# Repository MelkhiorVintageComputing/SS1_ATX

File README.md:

An adapter to use an ATX power supply with a Sun SPARCstation 1, 1+, 2, or Sun 3/80. Use at your own risk.

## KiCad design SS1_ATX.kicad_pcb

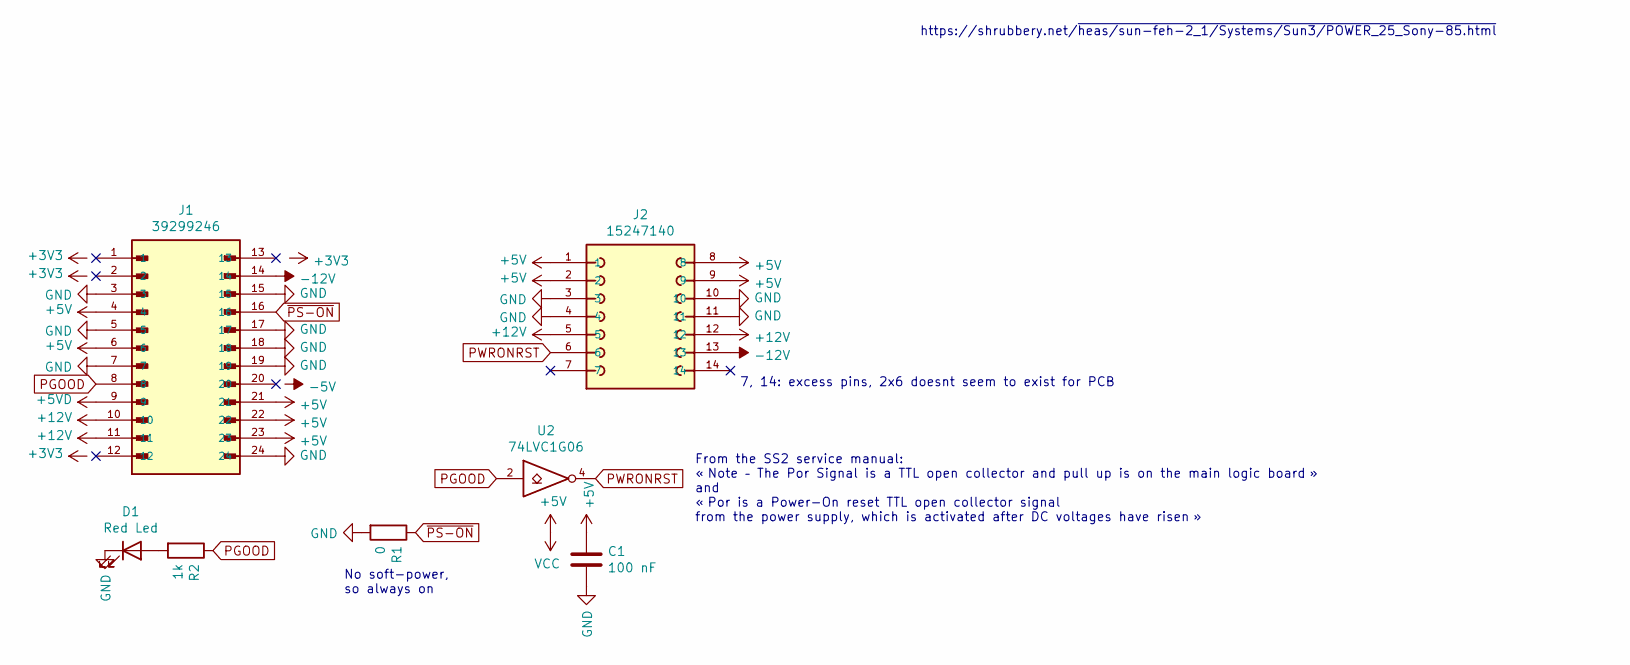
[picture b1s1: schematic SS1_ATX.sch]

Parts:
C1: 100 nF; C_0603_1608Metric; MPN CC0603KRX7R9BB104
D1: Red Led; LED_0805_2012Metric; MPN LTST-C170KRKT
J1: 39299246; MOLEX_39299246; PARTREV A1
J2: 15247140; MOLEX_15247140; PARTREV X5
R1: 0; R_0603_1608Metric; MPN 0603WAF0000T5E
R2: 1k; R_0603_1608Metric; MPN 0603WAF1001T5E
U2: 74LVC1G06; SOT-23-5; MPN SN74LVC1G06DBVR

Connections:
+5V: C1.2, J1.4, J1.6, J1.21, J1.22, J1.23, J2.1, J2.2, J2.8, J2.9, U2.5 (VCC)
+5VD: J1.9
+12V: J1.10, J1.11, J2.5, J2.12
-12V: J1.14, J2.13
GND: C1.1, D1.1 (K), J1.3, J1.5, J1.7, J1.15, J1.17, J1.18, J1.19, J1.24, J2.3, J2.4, J2.10, J2.11, R1.2, U2.3 (GND)
unnamed: D1.2 (A), R2.2
PGOOD: J1.8, R2.1, U2.2
PWRONRST: J2.6, U2.4
~PS-ON: J1.16, R1.1

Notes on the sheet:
From the SS2 service manual: « Note – The Por Signal is a TTL open collector and pull up is on the main logic board » and « Por is a Power-On reset TTL open collector signal from the power supply, which is activated after DC voltages have risen »
7, 14: excess pins, 2x6 doesnt seem to exist for PCB
https://shrubbery.net/~heas/sun-feh-2_1/Systems/Sun3/POWER_25_Sony-85.html
No soft-power, so always on

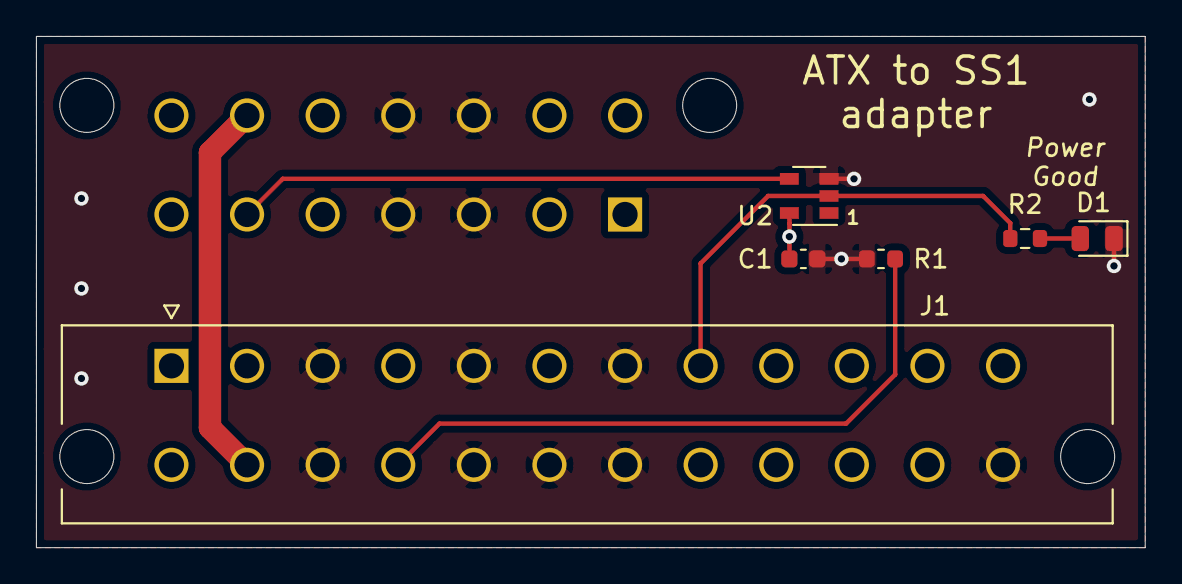
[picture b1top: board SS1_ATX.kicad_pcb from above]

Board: 4 copper layers, 61.6 x 28.4 mm, 7 parts (1 on the bottom side), 8 nets.

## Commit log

2023-05-01 initial draft
2023-05-01 oups, connect ~PS_ON to GND to turn on power
2023-05-04 more notes
2023-05-06 upd, notes
